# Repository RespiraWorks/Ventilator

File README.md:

# RespiraWorks Open Source Ventilator

</br>

This is a common repository for all hardware and software components of the RespiraWorks open source ventilator.

**If you intend to contribute, please read our [wiki](https://github.com/RespiraWorks/Ventilator/wiki) and [agreement](https://respiraworks.github.io/Ventilator/contributing/contributing.html).**

[RespiraWorks](https://respira.works/) is a 501(c)(3) non-profit organization with over 200 contributors worldwide working to design a low-cost and [open-source](open_source.md) ventilator for communities underserved by the global supply chain. Our objective is to provide the know-how and technology to enable local enterprises to manufacture and service these systems.

|           Most recent v0.4 rendering            |            Assembled v0.3 prototype             |
|:-----------------------------------------------:|:-----------------------------------------------:|
|  |  |

## Design Goals

We are dedicated to making this ventilator:
* [fully open source (software and hardware)](open_source.md)
* affordable (materials cost under US$2000)
* fully featured for extended clinical use through weaning and recovery
* vetted and filing-ready for regulatory review around the world
* optimized bill of materials to account for constrained supply chains
* designed for long-term clinical use beyond the pandemic

Most low-cost ventilator designs that have emerged in light of the COVID-19 crisis tackle the 'bridge' problem — keeping a patient alive for 6-8 hours of closely monitored care until they can be transitioned to a fully featured ventilator. We are designing that full ventilator, a highly valued medical device critical to care beyond the current crisis.

Our design shall provide essential features such as an intuitive, localized user interface, adaptive pressure- and volume-based operating modes, fine control of oxygen concentration, High Flow Nasal Cannula and other advanced features. What sets us apart from other similarly ambitious projects is our dedication to being fully open source. This repository embodies that promise.

We are targeting middle- and low-income parts of the world that will deal with COVID-19 for longer, with less access to healthcare, and a larger deficit of medical devices. We aim to deliver a design which meets the same operational rigors of current commercial ventilators, while addressing the high barrier to entry for such devices.

If you can lend your skills towards achieving this goal, please contact us at [join-us@respira.works](mailto:join-us@respira.works?subject=[GitHub]%20Join%20request). A list of roles we are looking to fill is also on our [website](https://respira.works/join-us).

## Project Status / Disclaimers

**This is an incomplete, as yet untested design that is not intended to be used on patients.**

**The repository contains live documents. There may be incomplete or contradictory information about various aspects of the design. Components may or may not connect and integrate as intended. Contents may also be out of date. If you decide to buy or build anything, do so at your own risk.**

We are currently in the process of designing our v0.4 prototype, plans whereof are captured in some of our outstanding [Milestones](https://github.com/RespiraWorks/Ventilator/milestones). The `master` branch of this repository includes bleeding edge changes in electrical, mechanical and software aspects of the project. Browse at your own peril.

For the latest stable and tested (but also obsolete) version of the design see the [Releases](https://github.com/RespiraWorks/Ventilator/releases) page.

## Repository Structure

* [**Documentation pages (outside of repository)**](https://respiraworks.github.io/Ventilator/index.html) - auto-generated pages (should eventually) include:
  * Requirements documentation
  * Regulatory documentation
  * Software documentation
  * Bill of materials for manufacturing
* [**Documentation source**](docs) - source files for the above pages
* [**System Design**](design) - describes the functional implementation and design theory of the system
* [**Manufacturing Design**](manufacturing) - describes the physical design of the ventilator and its components. Includes CAD models and notes on the manufacturing process
* [**Main Circuit Board**](pcb) - design, materials, assembly instructions for the ventilator main circuit board
* [**Software**](software) - source code for cycle controller and user interface, debug tools, and test scripts. Software architecture documentation is also here.
* [**Quality Assurance**](quality-assurance) - quality assurance strategy, testing plans, data

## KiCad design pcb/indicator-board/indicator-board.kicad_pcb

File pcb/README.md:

# Ventilator Mainboard 

This directory contains files for the Ventilator mainboard design.

The RespiraWorks Ventilator Mainboard PCB is a custom component that integrates the Cycle Controller, UI Computer,
sensors, actuator drives, power supplies, filtering, and protection components.

Due to the coupled nature of the controls, electrical, and mechanical components and their design the RespiraWorks
ventilator contains a custom fabricated printed circuit board (PCB) to connect the microcontroller, interface processor,
and sensor interfaces. The use of a custom PCB greatly reduces the chance for electrical assembly and fabrication errors
and is far more amenable to a quality fabrication process than hand-soldered components. We do not intend for this
component to be hand-assembled, and engineering turnkey fabrication instructions have been generated as part of the
submission; no assembly instructions are provided here.

The original Rev 1 PCB was done in Altium.  As of Rev A, this project has moved to KiCad for better accessibility.

## Rev A

The latest revision of the PCB is Rev A, designed to be used in the top-level design revision Ventilator v0.4.

The main design is in this folder and the project file is here: [Ventilator Mainboard Rev A](Ventilator.pro)

Recently exported files for PCB manufacture can be found on our Google Drive at
[Manufacturing/Output files v0.4/PCB](https://tinyurl.com/2p8af3fm).

This revision integrates many of the modules and daughter-cards in PCB Rev 1.0 into a single PCB, while breaking out the sensors to daughter-cards to make it better adaptable to sensors available in other markets.  It adds some important new features:
 - Moved CycleController from STM32L452 to STM32L496 microcontroller for more I/O pins, memory, and storage.
 - Added an independent FPGA-based supervisor.
 - Higher power capability now up to 120W.
 - Self-powered power loss alarm.
 - Integrated stepper drivers.
 - Ambient pressure sensing for altitude compensation.
 - Real time clock capability.
 - EEPROM for storing calibration data.
 - Additional pressure sensor channels to enable nested flow control.
 - Temperature sensors to monitor component health.
 - Integrated Li-Ion battery backup, charging, and monitoring.
 - Additional power connections for display, fans, and indicator lights.

## Sensor daughter-boards

> TODO: add documentation about these

## Rev 1.0

An archive of the previous version of the PCB, including the Altium-based design project and a snapshot of the old
readme is available on our Google Drive at
[Manufacturing/Output files v0.2-0.3/PCB](https://drive.google.com/drive/folders/1xHPLvo59tGI5uU38FrWMkVGmK_UR2sjQ?usp=sharing)

## Current issues

Issues for PCB work are tracked by tickets with the [PCB label](https://github.com/RespiraWorks/Ventilator/labels/pcb).

Somewhat related are the [Electrical design](https://github.com/RespiraWorks/Ventilator/labels/Electrical) issues.

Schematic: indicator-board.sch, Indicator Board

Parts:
D1, D2, D5: Green; LED_0805_2012Metric; Manufacturer PN LTST-C171KGKT
D3, D6: Yellow; LED_0805_2012Metric; Manufacturer PN LTST-C170KSKT
D4, D7: Red; LED_0805_2012Metric; Manufacturer PN LTST-C170KRKT
H1, H2, H3, H4: M2.5; MountingHole_2.7mm
J1: Cable to from main board; Molex_Micro-Fit_3.0_43650-0815_1x08_P3.00mm_Vertical; Manufacturer PN 43650-0815
R1, R2, R3, R4, R5, R6, R7: 1k; R_0603_1608Metric; Manufacturer PN RC0603FR-071KL

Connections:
+5V: J1.2, R1.1
/CC-LED-G: J1.3, R2.1
/CC-LED-R: J1.4, R4.1
/CC-LED-Y: J1.5, R3.1
/UI-LED-G: J1.6, R5.1
/UI-LED-R: J1.7, R7.1
/UI-LED-Y: J1.8, R6.1
GND: D1.1 (K), D2.1 (K), D3.1 (K), D4.1 (K), D5.1 (K), D6.1 (K), D7.1 (K), J1.1
unnamed: D1.2 (A), R1.2
unnamed: D2.2 (A), R2.2
unnamed: D3.2 (A), R3.2
unnamed: D4.2 (A), R4.2
unnamed: D5.2 (A), R5.2
unnamed: D6.2 (A), R6.2
unnamed: D7.2 (A), R7.2

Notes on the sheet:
Cycle Controller LEDs
UI Computer LEDs
Power LED

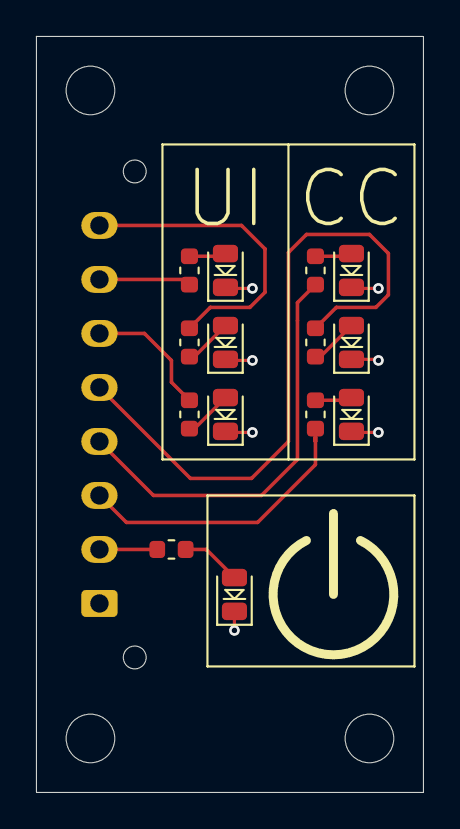
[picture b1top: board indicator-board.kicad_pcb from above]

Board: 4 copper layers, 21.5 x 42.0 mm, 19 parts (1 on the bottom side), 15 nets.

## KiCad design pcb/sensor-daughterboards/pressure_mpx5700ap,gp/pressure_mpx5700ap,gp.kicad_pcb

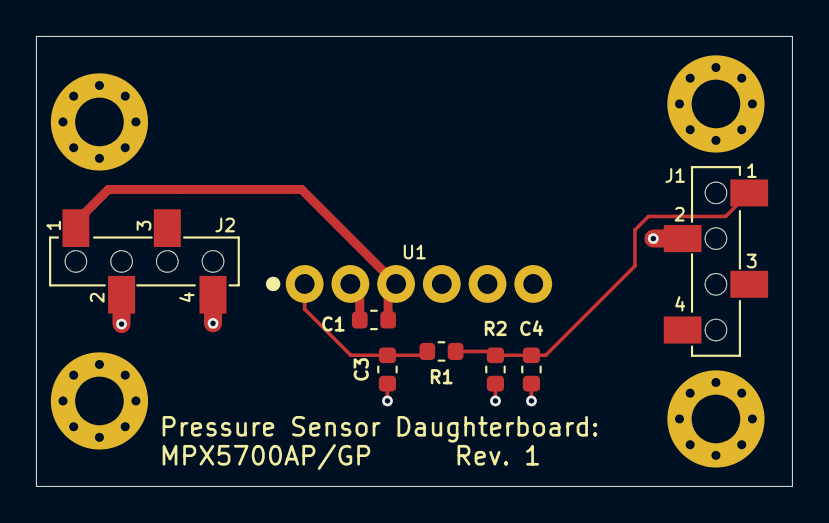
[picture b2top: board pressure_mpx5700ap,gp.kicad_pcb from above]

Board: 2 copper layers, 42.0 x 25.0 mm, 12 parts (0 on the bottom side), 4 nets.

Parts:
C1, C4: 1uF; C_0603_1608Metric
C3: 470pF; C_0603_1608Metric
H1, H2, H3, H4: M2.5; MountingHole_2.7mm_M2.5_Pad_Via
J1, J2: Main board connections (bottom entry); PinSocket_1x04_P2.54mm_Vertical_SMD_TE_1241152-4
R1: 2.4K; R_0603_1608Metric
R2: 4.7K; R_0603_1608Metric
U1: MPX5700AP/GP; NXP_MPX5700AP,GP_Vertical

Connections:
+5V_Sns: C1.2, J2.1, U1.3
GND: C1.1, C3.1, C4.1, J1.2, J2.2, J2.4, R2.1, U1.2
unnamed: C3.2, R1.2, U1.1
unnamed: C4.2, J1.1, R1.1, R2.2

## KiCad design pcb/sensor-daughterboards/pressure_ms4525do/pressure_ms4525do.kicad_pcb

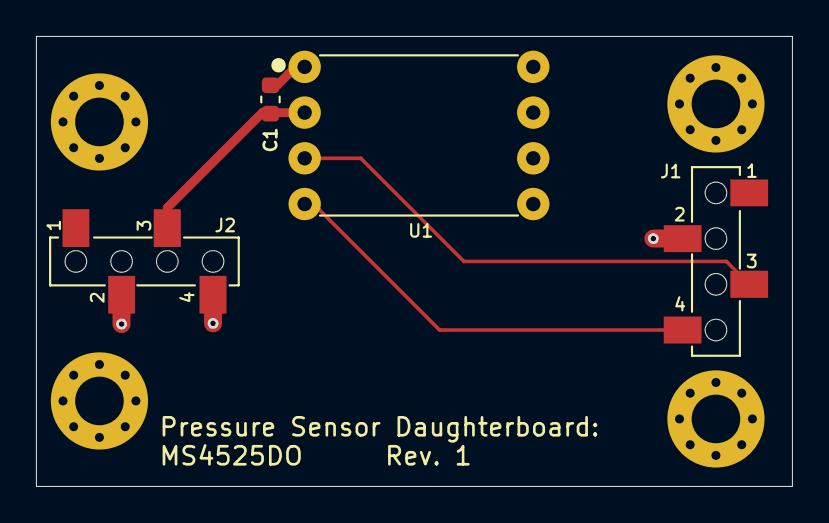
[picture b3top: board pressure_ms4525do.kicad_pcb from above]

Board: 2 copper layers, 42.0 x 25.0 mm, 8 parts (0 on the bottom side), 4 nets.

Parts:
C1: 1uF; C_0603_1608Metric
H1, H2, H3, H4: M2.5; MountingHole_2.7mm_M2.5_Pad_Via
J1, J2: Main board connections (bottom entry); PinSocket_1x04_P2.54mm_Vertical_SMD_TE_1241152-4
U1: MS4525DO-DS5AI001DP; TE_MS4525DO-DSxxxxxxDP

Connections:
+3.3V_Sns: C1.2, J2.3, U1.2
/SCL: J1.4, U1.4
/SDA: J1.3, U1.3
GND: C1.1, J1.2, J2.2, J2.4, U1.1

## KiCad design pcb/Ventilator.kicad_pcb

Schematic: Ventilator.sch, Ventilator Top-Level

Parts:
C186: 1uF; C_0603_1608Metric; Voltage 50V; Manufacturer PN C0805C105K5RACTU
D1: BAT54J; D_SOD-323F; Manufacturer PN BAT54J,115
F5: 1.1A 16V; Fuse_1812_4532Metric_Castellated; Manufacturer PN 0ZCG0110AF2C
H10, H11, H12, H13, H14: MountingHole_Pad; MountingHole_4.5mm_Pad
J53: Fan; Molex_Micro-Fit_3.0_43650-0215_1x02_P3.00mm_Vertical; Manufacturer PN 43650-0215
JP1, JP2, JP3: Jumper_NC_Small; SolderJumper-2_P1.3mm_Bridged_RoundedPad1.0x1.5mm
Q1, Q2: MMBT3904; SOT-23; Manufacturer PN MMBT3904-7-F
R1, R2, R3, R4, R5, R6, R7, R8: 1k; R_0603_1608Metric
R9, R18, R19: 4.7k; R_0603_1608Metric
R10, R11, R12, R13, R14, R15, R16, R17: 100k; R_0603_1608Metric
TP1, TP2, TP3, TP4, TP5, TP6, TP10, TP11, TP12, TP13, TP14, TP15, TP16, TP17, TP23, TP24, TP25, TP26, TP27, TP28, TP29, TP30, TP31, TP32, TP33, TP34: TP; TestPoint_Pad_2.0x2.0mm
TP7: PG-12V; TestPoint_Pad_2.0x2.0mm
TP8: PMon-IBat; TestPoint_Pad_2.0x2.0mm
TP9: PMon-IAdp; TestPoint_Pad_2.0x2.0mm
TP20: UART-Rx-STM-Tx-STLink; TestPoint_Pad_2.0x2.0mm
TP21: UART-Tx-STM-Rx-STLink; TestPoint_Pad_2.0x2.0mm
TP22: FPGA-ADC-nInt; TestPoint_Pad_2.0x2.0mm
TP35: PSol-CS1; TestPoint_Pad_2.0x2.0mm
TP36: CC-SDA; TestPoint_Pad_2.0x2.0mm
TP38: CC-SCL; TestPoint_Pad_2.0x2.0mm
TP39, TP40, TP41, TP42, TP44, TP45, TP46, TP47, TP50, TP51, TP52, TP53: TestPoint_Flag; TestPoint_Keystone_5019_Minature; Manufacturer PN 5019
TP43: PSol-CS2; TestPoint_Pad_2.0x2.0mm
TP48: UART-RTS-STM-CTS-RPi; TestPoint_Pad_2.0x2.0mm
TP49: UART-CTS-STM-RTS-RPi; TestPoint_Pad_2.0x2.0mm
TP54: UART-Tx-RPi-Rx-STM; TestPoint_Pad_2.0x2.0mm
TP55: UART-Rx-RPi-Tx-STM; TestPoint_Pad_2.0x2.0mm

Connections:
+3.3V_Ctrl: D1.1 (K), JP3.1, R5.2, R9.1, R18.1, R19.1; also elsewhere on the board
+12V: C186.1, F5.2; also elsewhere on the board
/Add'l aux functions/Blower-Enable: JP3.2; also elsewhere on the board
/Aux-I2C-Switch-nINT: JP2.2; also elsewhere on the board
/Bat-Alert: R3.1; also elsewhere on the board
/CC-SCL: R19.2, TP38.1; also elsewhere on the board
/CC-SDA: R18.2, TP36.1; also elsewhere on the board
/CC-Stepper-Reset: R4.1; also elsewhere on the board
/Cycle Controller/PH0: JP1.1, JP2.1, R9.2; also elsewhere on the board
/Exh-Flow: R11.2; also elsewhere on the board
/FPGA's ADC/ADC0: R10.1; also elsewhere on the board
/FPGA's ADC/ADC1: R11.1; also elsewhere on the board
/FPGA's ADC/ADC2: R12.1; also elsewhere on the board
/FPGA's ADC/ADC3: R13.1; also elsewhere on the board
/FPGA's ADC/ADC4: R14.1; also elsewhere on the board
/FPGA's ADC/ADC5: R15.1; also elsewhere on the board
/FPGA's ADC/ADC6: R16.1; also elsewhere on the board
/FPGA's ADC/ADC7: R17.1; also elsewhere on the board
/FPGA's ADC/nINT: TP22.1; also elsewhere on the board
/FPGA-Stepper-Reset: R6.2; also elsewhere on the board
/Inh-Flow: R10.2; also elsewhere on the board
/Low-Alarm-Bat: D1.2 (A), R2.1; also elsewhere on the board
/Mixing-Tank-Pressure: R15.2
/Oxygen-FiO2: R16.2; also elsewhere on the board
/Oxygen-Flow: R12.2; also elsewhere on the board
/Oxygen-Pressure: R14.2; also elsewhere on the board
/PSol Driver, Spare/CS: TP43.1; also elsewhere on the board
/PSol Driver/CS: TP35.1; also elsewhere on the board
/Patient-Pressure: R13.2; also elsewhere on the board
/Power Entry / Battery Handling/PG-12V: TP7.1; also elsewhere on the board
/Power Entry / Battery Handling/PMon-IAdp: TP9.1; also elsewhere on the board
/Power Entry / Battery Handling/PMon-IBat: TP8.1; also elsewhere on the board
/Safety FPGA/DIFF-RX-7+: TP31.1; also elsewhere on the board
/Safety FPGA/DIFF-RX-7-: TP32.1; also elsewhere on the board
/Safety FPGA/DIFF-RX-8+: TP29.1; also elsewhere on the board
/Safety FPGA/DIFF-RX-8-: TP30.1; also elsewhere on the board
/Safety FPGA/DIFF-RX-9+: TP27.1; also elsewhere on the board
/Safety FPGA/DIFF-RX-9-: TP28.1; also elsewhere on the board
/Safety FPGA/DIFF-RX-A+: TP25.1; also elsewhere on the board
/Safety FPGA/DIFF-RX-A-: TP26.1; also elsewhere on the board
/Safety FPGA/DIFF-RX-B+: TP23.1; also elsewhere on the board
/Safety FPGA/DIFF-RX-B-: TP24.1; also elsewhere on the board
/Safety FPGA/GPIO-11: TP33.1; also elsewhere on the board
/Safety FPGA/GPIO-12: TP34.1; also elsewhere on the board
/Stepper-nReset: Q1.3, Q2.3, R5.1; also elsewhere on the board
/SysMonADC-nINT: JP1.2; also elsewhere on the board
/UART-CTS-STM-RTS-RPi: TP49.1
/UART-RTS-RPi-CTS-STM: R1.1; also elsewhere on the board
/UART-RTS-STM-CTS-RPi: TP48.1
/UART-Rx-RPi-Tx-STM: TP55.1; also elsewhere on the board
/UART-Rx-STM-Tx-STLink: TP20.1; also elsewhere on the board
/UART-Tx-FPGA-Rx-RPi: R7.2; also elsewhere on the board
/UART-Tx-RPi-Rx-STM: R8.2, TP54.1; also elsewhere on the board
/UART-Tx-STM-Rx-STLink: TP21.1; also elsewhere on the board
/UI Computer/GPIO0(ID_SD): TP10.1; also elsewhere on the board
/UI Computer/GPIO1(ID_SC): TP11.1; also elsewhere on the board
/UI Computer/GPIO2(SDA): TP12.1; also elsewhere on the board
/UI Computer/GPIO3(SCL): TP13.1; also elsewhere on the board
/UI Computer/GPIO7(CE1): TP14.1; also elsewhere on the board
/UI Computer/GPIO9(MISO): R7.1; also elsewhere on the board
/UI Computer/GPIO10(MOSI): TP15.1; also elsewhere on the board
/UI Computer/GPIO11(SCLK): TP16.1; also elsewhere on the board
/UI Computer/GPIO13(PWM1): TP17.1; also elsewhere on the board
/UI Computer/GPIO14(TXD): R8.1; also elsewhere on the board
/UI Computer/GPIO17: R1.2; also elsewhere on the board
/UI Computer/GPIO18(PCM_CLK): R2.2; also elsewhere on the board
/UI Computer/GPIO19(PCM_FS): R3.2; also elsewhere on the board
/UI Computer/GPIO20(PCM_DIN): TP1.1; also elsewhere on the board
/UI Computer/GPIO21(PCM_DOUT): TP2.1; also elsewhere on the board
/UI Computer/GPIO22: TP3.1; also elsewhere on the board
/UI Computer/GPIO23: TP4.1; also elsewhere on the board
/UI Computer/GPIO24: TP5.1; also elsewhere on the board
/UI Computer/GPIO27: TP6.1; also elsewhere on the board
/Vin-Sense: R17.2; also elsewhere on the board
GND: C186.2, J53.1, Q1.2, Q2.2, TP39.1, TP40.1, TP41.1, TP42.1, TP44.1, TP45.1, TP46.1, TP47.1, TP50.1, TP51.1, TP52.1, TP53.1; also elsewhere on the board
unnamed: F5.1, J53.2
unnamed: Q1.1, R4.2
unnamed: Q2.1, R6.1

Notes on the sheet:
Series resistors prevent FPGA ADC faults from disrupting critical analog signals
Either cycle controller or FPGA can shut down stepper drivers
Series resistors on signals received by UI computer prevents problems driving these signals if UI computer loses power
Unless noted otherwise: - Resistors are 1% tolerance - Capacitors < 47 nF are 5% tolerance - Capacitors ≥ 47 nF are 10% tolerance
Global I2C pull-ups

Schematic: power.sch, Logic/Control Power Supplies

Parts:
C1: 33uF; CP_Elec_6.3x7.7; Voltage 50V; Manufacturer PN EEE-FK1H330XP
D2, D3: BAT54J; D_SOD-323F; Manufacturer PN BAT54J,115
Q3: MMBT3904; SOT-23; Manufacturer PN MMBT3904-7-F
R20, R21: 1k; R_0603_1608Metric
R22: 0; R_0603_1608Metric
TP56: TP; TestPoint_Pad_2.0x2.0mm
TP57, TP58: TestPoint_Flag; TestPoint_Keystone_5019_Minature; Manufacturer PN 5019

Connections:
+5V: D2.2 (A), R22.1; also elsewhere on the board
+5V_Sns: C1.1, R22.2, TP58.1; also elsewhere on the board
+5V_USB: D3.2 (A); also elsewhere on the board
/Logic/Control Power Supplies/3.3V Logic Supply/In: D2.1 (K), D3.1 (K), TP57.1; also elsewhere on the board
/Logic/Control Power Supplies/5V UI Supply/nEnable: Q3.3; also elsewhere on the board
/UI-Power-Off: R20.1, R21.1, TP56.1; also elsewhere on the board
GND: C1.2, Q3.2, R20.2; also elsewhere on the board
unnamed: Q3.1, R21.2

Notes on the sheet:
Optional filter
5V Power Supplies
Diode-ORing for +3.3V Ctrl, so that the CC can be powered from the STM programmer's USB connection alone, for programming and firmware debug
3.3V Power Supplies

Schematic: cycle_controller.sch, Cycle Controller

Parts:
BT1: CR2016; BatteryHolder_CR2016_MPD_BLP2016SM-G; Manufacturer PN BLP2016SM-GTR
C26, C32, C36, C37, C38, C39, C40, C41, C43: 100nF; C_0603_1608Metric; Voltage 50V; Manufacturer PN C0603C104K5RACTU
C27, C28: TBD; C_0603_1608Metric
C29, C30: 18pF; C_0603_1608Metric; Voltage 50V; Manufacturer PN C0603C180J5GACTU
C31, C35, C44: 1uF; C_0603_1608Metric; Voltage 50V; Manufacturer PN C0805C105K5RACTU
C33, C34: 6.8pF; C_0603_1608Metric; Voltage 50V; Manufacturer PN C0603C689J5GACTU
C42: 10uF; C_1210_3225Metric; Voltage 100V; Manufacturer PN GRM32EC72A106KE05L
J1: Optical end stop 1; Molex_Micro-Fit_3.0_43650-0315_1x03_P3.00mm_Vertical; Manufacturer PN 43650-0315
J2: Optical end stop 2; Molex_Micro-Fit_3.0_43650-0315_1x03_P3.00mm_Vertical; Manufacturer PN 43650-0315
J3: 503182-1852; SD_Molex_5031821852; Manufacturer PN 503182-1852
J4, J7: Arduino Connector; PinSocket_1x08_P2.54mm_Vertical; Manufacturer PN PPPC081LFBN-RC
J5: Arduino Connector; PinSocket_1x06_P2.54mm_Vertical; Manufacturer PN PPPC061LFBN-RC
J6: Arduino Connector; PinSocket_1x10_P2.54mm_Vertical; Manufacturer PN PPPC101LFBN-RC
JP6: Jumper; SolderJumper-2_P1.3mm_Open_RoundedPad1.0x1.5mm
JP7: Jumper; SolderJumper-2_P1.3mm_Bridged_RoundedPad1.0x1.5mm
R37, R44: 10k; R_0603_1608Metric
R38: 100; R_0603_1608Metric
R39, R40, R42, R43, R45, R46, R47, R48, R49: 0; R_0603_1608Metric
R41: 4.7k; R_0603_1608Metric
SW1: User TBD; SW_Push_6x6; Manufacturer PN PTS645SK50SMTR92 LFS
SW2: Reset CC; SW_Push_6x6; Manufacturer PN PTS645SK50SMTR92 LFS
TP67: SPI-MISO; TestPoint_Pad_2.0x2.0mm
TP68: SPI-MOSI; TestPoint_Pad_2.0x2.0mm
TP69: SPI-SCLK; TestPoint_Pad_2.0x2.0mm
TP70: uSD-nCS; TestPoint_Pad_2.0x2.0mm
TP71: PD3; TestPoint_Pad_2.0x2.0mm
TP72: PD4; TestPoint_Pad_2.0x2.0mm
TP73: PD5; TestPoint_Pad_2.0x2.0mm
TP74: PD6; TestPoint_Pad_2.0x2.0mm
TP75: PE0; TestPoint_Pad_2.0x2.0mm
TP76: PE1; TestPoint_Pad_2.0x2.0mm
TP77: PE2; TestPoint_Pad_2.0x2.0mm
TP78: PE3; TestPoint_Pad_2.0x2.0mm
U5: STM32L496VGT; LQFP-100_14x14mm_P0.5mm; Manufacturer PN STM32L496VGT6
U31: ShieldConnectors; stm32shield
Y1: 8 Mhz; Crystal_SMD_HC49-SD; Manufacturer PN ABLS-8.000MHZ-B4-T
Y2: 32.768 kHz; Crystal_SMD_Abracon_ABS25; Manufacturer PN ABS25-32.768KHZ-6-T

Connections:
+3.3V_Ctrl: C31.1, C32.1, C38.1, C39.1, C40.1, C41.1, C42.1, J3.4 (VDD), J4.2, J4.4, JP6.2, R37.1, R41.2, U5.11, U5.28, U5.50, U5.73, U5.75, U5.100; also elsewhere on the board
+3.3V_Ctrl_A: J6.8
+3.3V_Sns: C43.1, C44.1, R45.2, U5.22; also elsewhere on the board
+5V: J1.1, J4.5, J4.8; also elsewhere on the board
/Bat-Alert: U5.77; also elsewhere on the board
/Blower-Ctrl: U5.63; also elsewhere on the board
/CC-Buzzer: J7.6, U5.53; also elsewhere on the board
/CC-LED-G: J5.3, U5.67; also elsewhere on the board
/CC-LED-R: U5.65; also elsewhere on the board
/CC-LED-Y: U5.66; also elsewhere on the board
/CC-SCL: J6.10, U5.95; also elsewhere on the board
/CC-SDA: J6.9, U5.96; also elsewhere on the board
/CC-Stepper-Reset: J7.3, U5.48; also elsewhere on the board
/Cycle Controller/BOOT0: R44.2, U5.94
/Cycle Controller/PH0: R42.1, U5.12; also elsewhere on the board
/Cycle Controller/RTC-Batt: BT1.1 (+), C35.1, JP6.1, U5.6
/Cycle Controller/Stepper-Lim-Sw1: C27.2, R39.1, U5.78
/Cycle Controller/Stepper-Lim-Sw2: C28.2, R40.1, U5.79
/Cycle Controller/USD-MISO: J6.5
/Cycle Controller/USD-MOSI: J6.4
/Cycle Controller/USD-SCLK: J6.6
/Cycle Controller/uSD-Detect: J3.Detect (DT), R37.2, U5.64
/Cycle Controller/uSD-nCS: J3.2 (CD/DAT3), TP70.1, U5.29
/Exh-Flow: U5.33; also elsewhere on the board
/Inh-Flow: J5.2, U5.24; also elsewhere on the board
/Mix-Tank-Pressure: U5.17; also elsewhere on the board
/Oxygen-FiO2: J5.6, U5.15; also elsewhere on the board
/Oxygen-Flow: U5.34; also elsewhere on the board
/Oxygen-Pressure: U5.18; also elsewhere on the board
/PMon-ACOK: J5.4, U5.92; also elsewhere on the board
/PSol1-Ctrl: J6.1, U5.47; also elsewhere on the board
/PSol1-nFault: U5.93; also elsewhere on the board
/PSol2-Ctrl: U5.23; also elsewhere on the board
/PSol2-nFault: R43.1, U5.13; also elsewhere on the board
/Patient-Pressure: J5.5, U5.16; also elsewhere on the board
/STM Programmer for cycle controller/CC-SWCLK: U5.76; also elsewhere on the board
/STM Programmer for cycle controller/CC-SWDIO: U5.72; also elsewhere on the board
/STM Programmer for cycle controller/CC-SWO: U5.89; also elsewhere on the board
/STM Programmer for cycle controller/CC-nRST: C37.1, J4.3, SW2.1, U5.14; also elsewhere on the board
/Stepper1-StCk: U5.35; also elsewhere on the board
/Stepper1-nBusy: J6.3, U5.51; also elsewhere on the board
/Stepper2-StCk: J7.8, U5.36; also elsewhere on the board
/Stepper2-nBusy: J6.2, U5.52; also elsewhere on the board
/Stepper-MISO: J3.7 (DAT0), TP67.1, U5.31; also elsewhere on the board
/Stepper-MOSI: J3.3 (CMD), TP68.1, U5.32; also elsewhere on the board
/Stepper-SCK: J3.5 (CLK), TP69.1, U5.30; also elsewhere on the board
/Stepper-nCS: J7.5, U5.54; also elsewhere on the board
/Stepper-nFlag: J7.4, U5.37; also elsewhere on the board
/UART-CTS-RPi-RTS-STM: U5.71; also elsewhere on the board
/UART-CTS-STM-RTS-FPGA: U5.91; also elsewhere on the board
/UART-RTS-RPi-CTS-STM: U5.70; also elsewhere on the board
/UART-RTS-STM-CTS-FPGA: U5.90; also elsewhere on the board
/UART-Rx-RPi-Tx-STM: J7.2, U5.68; also elsewhere on the board
/UART-Rx-STM-Tx-FPGA: U5.83; also elsewhere on the board
/UART-Rx-STM-Tx-STLink: U5.26; also elsewhere on the board
/UART-Tx-RPi-Rx-STM: J7.1, U5.69; also elsewhere on the board
/UART-Tx-STM-Rx-FPGA: U5.80; also elsewhere on the board
/UART-Tx-STM-Rx-STLink: J7.7, U5.25; also elsewhere on the board
GND: BT1.2 (-), C27.1, C28.1, C29.1, C30.1, C31.2, C32.2, C33.2, C34.2, C35.2, C36.2, C37.2, C38.2, C39.2, C40.2, C41.2, C42.2, J1.3, J2.3, J3.6 (VSS), J3.9 (Shield), J4.6, J4.7, J6.7, JP7.1, R38.2, R44.1, R46.1, R47.1, SW1.2, SW2.2, U5.10, U5.27, U5.49, U5.74, U5.99; also elsewhere on the board
GNDA: C43.2, C44.2, JP7.2, U5.19, U5.20
unnamed: C26.1, R41.1, SW1.1, U5.7
unnamed: C26.2, R38.1
unnamed: C29.2, R42.2, Y1.1
unnamed: C30.2, R43.2, Y1.2
unnamed: C33.1, R47.2, R48.2, Y2.1
unnamed: C34.1, R46.2, R49.2, Y2.4
unnamed: C36.1, R45.1, U5.21
unnamed: J1.2, J2.1, R39.2
unnamed: J2.2, R40.2
unnamed: R48.1, U5.8
unnamed: R49.1, U5.9
unnamed: TP71.1, U5.84
unnamed: TP72.1, U5.85
unnamed: TP73.1, U5.86
unnamed: TP74.1, U5.87
unnamed: TP75.1, U5.97
unnamed: TP76.1, U5.98
unnamed: TP77.1, U5.1
unnamed: TP78.1, U5.2

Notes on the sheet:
VDD pins
VDDA pin
Boots from main Flash memory by default
MicroSD Card Connector
Arduino headers for expansion
D10
D11
D12
D13
D18/SDA
D19/SCL
AREF
VIN
IOREF
RESET
Uses MSI internal 4 Mhz clock by default

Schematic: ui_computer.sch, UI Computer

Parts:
C45: 100nF; C_0603_1608Metric; Voltage 50V; Manufacturer PN C0603C104K5RACTU
C46: 1uF; C_0603_1608Metric; Voltage 50V; Manufacturer PN C0805C105K5RACTU
H1: RaspberryPi
J8: Raspberry Pi; PinSocket_2x20_P2.54mm_Vertical; Manufacturer PN ESQ-120-44-L-D
J9: Touchscreen power; Molex_Micro-Fit_3.0_43045-0212_2x01_P3.00mm_Vertical; Manufacturer PN 43045-0212
R50, R51, R52, R53: 0; R_0603_1608Metric

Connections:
+3V3_Rpi: J8.1, J8.17, R50.1, R52.1
+5V_GUI: C45.1, C46.1, J8.2, J8.4, J9.2; also elsewhere on the board
/GUI-Buzzer: J8.32; also elsewhere on the board
/UART-CTS-RPi-RTS-STM: J8.36; also elsewhere on the board
/UART-Rx-FPGA-Tx-RPi: J8.24; also elsewhere on the board
/UART-Rx-RPi-Tx-STM: J8.10; also elsewhere on the board
/UI Computer/GPIO0(ID_SD): J8.27; also elsewhere on the board
/UI Computer/GPIO1(ID_SC): J8.28; also elsewhere on the board
/UI Computer/GPIO2(SDA): J8.3; also elsewhere on the board
/UI Computer/GPIO3(SCL): J8.5; also elsewhere on the board
/UI Computer/GPIO7(CE1): J8.26; also elsewhere on the board
/UI Computer/GPIO9(MISO): J8.21; also elsewhere on the board
/UI Computer/GPIO10(MOSI): J8.19; also elsewhere on the board
/UI Computer/GPIO11(SCLK): J8.23; also elsewhere on the board
/UI Computer/GPIO13(PWM1): J8.33; also elsewhere on the board
/UI Computer/GPIO14(TXD): J8.8; also elsewhere on the board
/UI Computer/GPIO17: J8.11; also elsewhere on the board
/UI Computer/GPIO18(PCM_CLK): J8.12; also elsewhere on the board
/UI Computer/GPIO19(PCM_FS): J8.35; also elsewhere on the board
/UI Computer/GPIO20(PCM_DIN): J8.38; also elsewhere on the board
/UI Computer/GPIO21(PCM_DOUT): J8.40; also elsewhere on the board
/UI Computer/GPIO22: J8.15; also elsewhere on the board
/UI Computer/GPIO23: J8.16; also elsewhere on the board
/UI Computer/GPIO24: J8.18; also elsewhere on the board
/UI Computer/GPIO27: J8.13; also elsewhere on the board
/UI Computer/UI_ID0: J8.22, R52.2, R53.1
/UI Computer/UI_ID1: J8.37, R50.2, R51.1
/UI-LED-G: J8.7; also elsewhere on the board
/UI-LED-R: J8.29; also elsewhere on the board
/UI-LED-Y: J8.31; also elsewhere on the board
GND: C45.2, C46.2, H1.1, J8.6, J8.9, J8.14, J8.20, J8.25, J8.30, J8.34, J8.39, J9.1, R51.2, R53.2; also elsewhere on the board

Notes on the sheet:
RPI powered by 5V
USB TO UART adapter: https://www.ftdichip.com/Support/Documents/DataSheets/Modules/DS_DB9-USB-RS232.pdf

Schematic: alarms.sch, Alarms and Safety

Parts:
C47, C50, C53: 100nF; C_0603_1608Metric; Voltage 50V; Manufacturer PN C0603C104K5RACTU
C48: 33uF; CP_Elec_6.3x7.7; Voltage 50V; Manufacturer PN EEE-FK1H330XP
C49: 1uF; C_0603_1608Metric; Voltage 50V; Manufacturer PN C0805C105K5RACTU
C51, C52, C54, C55: 10nF; C_0603_1608Metric; Voltage 50V; Manufacturer PN GRM1885C1H103JA01D
D8: 2.0V; D_SOD-123; Manufacturer PN MMSZ4679T1G
D9, D10: 3.3V; D_SOD-123; Manufacturer PN MMSZ4684T1G
D11, D12, D13, D14: 1N4448W; D_SOD-123; Manufacturer PN 1N4448W-7-F
J10: Alarm Battery (4x AA); Molex_Micro-Fit_3.0_43650-0415_1x04_P3.00mm_Vertical; Manufacturer PN 43650-0415
Q4, Q5, Q6, Q8, Q9, Q11, Q12, Q13: MMBT3904; SOT-23; Manufacturer PN MMBT3904-7-F
Q7, Q10: MMBT2907A; SOT-23; Manufacturer PN MMBT2907A-7-F
R54, R55, R56, R57, R58, R59, R60, R61, R65, R68, R76, R81, R84: 10k; R_0603_1608Metric
R62, R77, R78: 1M; R_0603_1608Metric
R63, R66, R71, R72: 100k; R_0603_1608Metric
R64: 2k; R_0603_1608Metric
R67: 442k; R_0603_1608Metric
R69: 52.3k; R_0603_1608Metric
R70: 249k; R_0603_1608Metric
R73, R74, R79, R80, R82, R83, R85, R86: 1k; R_0603_1608Metric
R75: 680; R_0603_1608Metric
S1, S2, S3, S4: CT-1205H-SMT; CT-1205H-SMT-TR; Manufacturer PN CT-1205H-SMT-TR
TP79: PD-Alarm; TestPoint_Pad_2.0x2.0mm
TP80, TP81, TP82, TP83, TP84, TP85: TP; TestPoint_Pad_2.0x2.0mm
U6, U7: TLC555; SOIC-8_3.9x4.9mm_P1.27mm; Manufacturer PN TLC555QDR
U8: TL431LI; SOT-23; Manufacturer PN TL431LIAIDBZR

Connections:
+3.3V_Ctrl: D8.1 (K); also elsewhere on the board
+5V: D9.1 (K), D10.1 (K), D11.2 (A), S2.1, S3.1; also elsewhere on the board
+5V_GUI: S4.1; also elsewhere on the board
+BATT: C48.1, C50.2, C53.2, D11.1 (K), Q7.3, Q10.2, R56.2, R61.2, R66.2, R69.2, R75.2, S1.1, U6.8 (VCC), U7.8 (VCC)
/Alarms and Power Monitoring/Alarm-Bat: D14.2 (A), J10.1, R71.1
/Alarms and Power Monitoring/Low-Alarm-Bat: Q10.3, R78.1, R81.1, R84.1, TP84.1
/Alarms and Power Monitoring/PD-Alarm: C47.2, D12.1 (K), D13.1 (K), R63.2, TP79.1, U6.4 (Reset)
/CC-Buzzer: R79.1, TP82.1; also elsewhere on the board
/FPGA-Buzzer: R82.1, TP83.1; also elsewhere on the board
/GUI-Buzzer: R85.1, TP85.1; also elsewhere on the board
/Low-Alarm-Bat: R84.2; also elsewhere on the board
GND: C47.1, C48.2, C49.1, C50.1, C51.1, C52.1, C53.1, C54.1, C55.1, J10.3, Q4.2, Q5.2, Q6.2, Q8.2, Q9.2, Q11.2, Q12.2, Q13.2, R54.1, R57.1, R58.1, R63.1, R72.2, R74.2, R80.2, R81.2, R83.2, R86.2, U6.1 (GND), U7.1 (GND), U8.3 (A); also elsewhere on the board
unnamed: C49.2, R67.1, U6.2 (Trig), U6.6 (Thresh)
unnamed: C51.2, U6.5 (Cont)
unnamed: C52.2, R70.1, U7.2 (Trig), U7.6 (Thresh)
unnamed: C54.2, U7.5 (Cont)
unnamed: C55.2, R71.2, R72.1, R77.2, TP81.1, U8.2 (REF)
unnamed: D8.2 (A), R54.2, R55.2
unnamed: D9.2 (A), R57.2, R59.2
unnamed: D10.2 (A), R58.2, R60.2
unnamed: D12.2 (A), Q4.3, R56.1
unnamed: D13.2 (A), Q5.3, R61.1
unnamed: D14.1 (K), Q7.2, R65.2, R68.2
unnamed: Q4.1, R55.1
unnamed: Q5.1, R59.1
unnamed: Q6.1, R60.1, R62.2
unnamed: Q6.3, Q8.1, R68.1
unnamed: Q7.1, R64.2, R65.1
unnamed: Q8.3, R62.1, R64.1
unnamed: Q9.1, R73.2, R74.1, TP80.1
unnamed: Q9.3, S1.2
unnamed: Q10.1, R76.2
unnamed: Q11.1, R79.2, R80.1
unnamed: Q11.3, S2.2
unnamed: Q12.1, R82.2, R83.1
unnamed: Q12.3, S3.2
unnamed: Q13.1, R85.2, R86.1
unnamed: Q13.3, S4.2
unnamed: R66.1, R67.2, U6.7 (Disch)
unnamed: R69.1, R70.2, U7.7 (Disch)
unnamed: R73.1, U7.3 (Q)
unnamed: R75.1, R76.1, U8.1 (K)
unnamed: R77.1, R78.2
unnamed: U6.3 (Q), U7.4 (Reset)

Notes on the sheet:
Power-down alarm
C4 (~~261 Hz) oscillator
~~1 Hz oscillator
Threshold ~~2.4-2.9V
Sounds power-down alarm (powered from alarm battery) if any of the main power rails go down
Threshold ~~3.5-4.2V
10K resistors provide ~~50uA nominal through zeners near threshold input voltage; 1K resistor provides ~~0.5mA through BAS21 near threshold input voltage
~~1 ms filter
All 2.4 kHz, 88 dbA @ 5V
Software alarms
Power ORing from alarm battery
PNP circuit disables alarm battery output when +5V is present, even though battery voltage is higher than 5V
~~0.6 mA battery load
Optional hysteresis
Low alarm battery monitor
Low battery threshold 5.1V (semi-arbitrary) Threshold ~~= 2.495V * ((Rlow||Rhyst)+Rhigh)/(Rlow||Rhyst)
~~38-75 mV hysteresis (on REF pin) Hysteresis = (+5V_Batt - 2.495V)/Rhyst*(Rhigh || Rlow) (only valid @ trip point when TL431's REF pin = 2.495V; larger hysteresis when REF voltage is lower because battery voltage is << threshold voltage)
Limits current to FPGA and/or CC and/or RPi input (150µA max.), clamped to 3.3V by ext. Schottkys
~~25µA battery load
1 mA min. required cathode current when on, 1 µA max. cathode current drawn when off
Rlow
Rhigh
0.4µA max. into ref. pin
On: Cathode current = 2.2 mA (low batt.) to 4.4 mA (+5V) Vbe=1.5V min. (before resistor) → Ib=150µA min. Off: Vbe < 1 mV
Rhyst
+5V_Batt voltage range is about 4V (+5V minus large diode Vf) to 5.5V (6V battery minus small diode Vf)
Alternate output for indicator LED, etc.
2mA Ib, can support ~~200 mA load on +5V_Batt

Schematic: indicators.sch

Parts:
J11: Cable to indicator board; Molex_Micro-Fit_3.0_43650-0815_1x08_P3.00mm_Vertical; Manufacturer PN 43650-0815

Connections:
+5V: J11.2; also elsewhere on the board
/CC-LED-G: J11.3; also elsewhere on the board
/CC-LED-R: J11.4; also elsewhere on the board
/CC-LED-Y: J11.5; also elsewhere on the board
/UI-LED-G: J11.6; also elsewhere on the board
/UI-LED-R: J11.7; also elsewhere on the board
/UI-LED-Y: J11.8; also elsewhere on the board
GND: J11.1; also elsewhere on the board

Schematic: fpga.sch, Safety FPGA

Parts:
H15: FPGAOutline; BEMICRO-MAX10
J12: Mates J4 on BeMicro MAX10; PinSocket_2x20_P2.54mm_Vertical; Manufacturer PN ESW-120-33-G-D
J13: Mates J5 on BeMicro MAX10; PinSocket_2x20_P2.54mm_Vertical; Manufacturer PN ESW-120-33-G-D
R87, R88: 4.7k; R_0603_1608Metric
R89: 0; R_1206_3216Metric

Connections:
+5V: R89.2; also elsewhere on the board
/FPGA-Buzzer: J13.1; also elsewhere on the board
/FPGA-Stepper-Reset: J13.7; also elsewhere on the board
/Safety FPGA/DIFF-RX-0+: J13.39
/Safety FPGA/DIFF-RX-0-: J13.40
/Safety FPGA/DIFF-RX-1+: J13.37
/Safety FPGA/DIFF-RX-1-: J13.38
/Safety FPGA/DIFF-RX-2+: J13.35
/Safety FPGA/DIFF-RX-2-: J13.36
/Safety FPGA/DIFF-RX-3+: J13.33
/Safety FPGA/DIFF-RX-3-: J13.34
/Safety FPGA/DIFF-RX-4+: J13.31
/Safety FPGA/DIFF-RX-4-: J13.32
/Safety FPGA/DIFF-RX-5+: J13.27
/Safety FPGA/DIFF-RX-5-: J13.28
/Safety FPGA/DIFF-RX-6+: J13.25
/Safety FPGA/DIFF-RX-6-: J13.26
/Safety FPGA/DIFF-RX-7+: J13.23; also elsewhere on the board
/Safety FPGA/DIFF-RX-7-: J13.24; also elsewhere on the board
/Safety FPGA/DIFF-RX-8+: J13.21; also elsewhere on the board
/Safety FPGA/DIFF-RX-8-: J13.22; also elsewhere on the board
/Safety FPGA/DIFF-RX-9+: J13.19; also elsewhere on the board
/Safety FPGA/DIFF-RX-9-: J13.20; also elsewhere on the board
/Safety FPGA/DIFF-RX-A+: J13.17; also elsewhere on the board
/Safety FPGA/DIFF-RX-A-: J13.18; also elsewhere on the board
/Safety FPGA/DIFF-RX-B+: J13.15; also elsewhere on the board
/Safety FPGA/DIFF-RX-B-: J13.16; also elsewhere on the board
/Safety FPGA/GPIO-11: J13.13; also elsewhere on the board
/Safety FPGA/GPIO-12: J13.14; also elsewhere on the board
/Safety FPGA/GPIO-A: J12.5
/Safety FPGA/GPIO-B: J12.6
/Safety FPGA/I2C-SCL-FPGA: J12.4, R88.2; also elsewhere on the board
/Safety FPGA/I2C-SDA-FPGA: J12.3, R87.2; also elsewhere on the board
/Safety FPGA/LVDS-TX-0+: J12.40
/Safety FPGA/LVDS-TX-0-: J12.39
/Safety FPGA/LVDS-TX-1+: J12.38
/Safety FPGA/LVDS-TX-1-: J12.37
/Safety FPGA/LVDS-TX-2+: J12.36
/Safety FPGA/LVDS-TX-2-: J12.35
/Safety FPGA/LVDS-TX-3+: J12.32
/Safety FPGA/LVDS-TX-3-: J12.31
/Safety FPGA/LVDS-TX-4+: J12.30
/Safety FPGA/LVDS-TX-4-: J12.29
/Safety FPGA/LVDS-TX-5+: J12.28
/Safety FPGA/LVDS-TX-5-: J12.27
/Safety FPGA/LVDS-TX-6+: J12.24
/Safety FPGA/LVDS-TX-6-: J12.23
/Safety FPGA/LVDS-TX-7+: J12.22
/Safety FPGA/LVDS-TX-7-: J12.21
/Safety FPGA/LVDS-TX-8+: J12.20
/Safety FPGA/LVDS-TX-8-: J12.19
/Safety FPGA/LVDS-TX-9+: J12.16
/Safety FPGA/LVDS-TX-9-: J12.15
/Safety FPGA/LVDS-TX-A+: J12.14
/Safety FPGA/LVDS-TX-A-: J12.13
/Safety FPGA/LVDS-TX-B+: J12.12
/Safety FPGA/LVDS-TX-B-: J12.11
/UART-CTS-STM-RTS-FPGA: J13.9; also elsewhere on the board
/UART-RTS-STM-CTS-FPGA: J13.8; also elsewhere on the board
/UART-Rx-FPGA-Tx-RPi: J13.5; also elsewhere on the board
/UART-Rx-STM-Tx-FPGA: J13.3; also elsewhere on the board
/UART-Tx-FPGA-Rx-RPi: J13.6; also elsewhere on the board
/UART-Tx-STM-Rx-FPGA: J13.4; also elsewhere on the board
/UI-Power-Off: J13.2; also elsewhere on the board
/VSys-Power-Off: J13.10; also elsewhere on the board
GND: J12.7, J12.8, J12.9, J12.10, J12.17, J12.18, J12.25, J12.26, J12.33, J12.34, J13.12, J13.30; also elsewhere on the board
unnamed: J13.11, R89.1

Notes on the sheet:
+3.3V_FPGA comes from FPGA board
Place for optional fuse
BeMicro MAX10 board has onboard I2C pull-ups

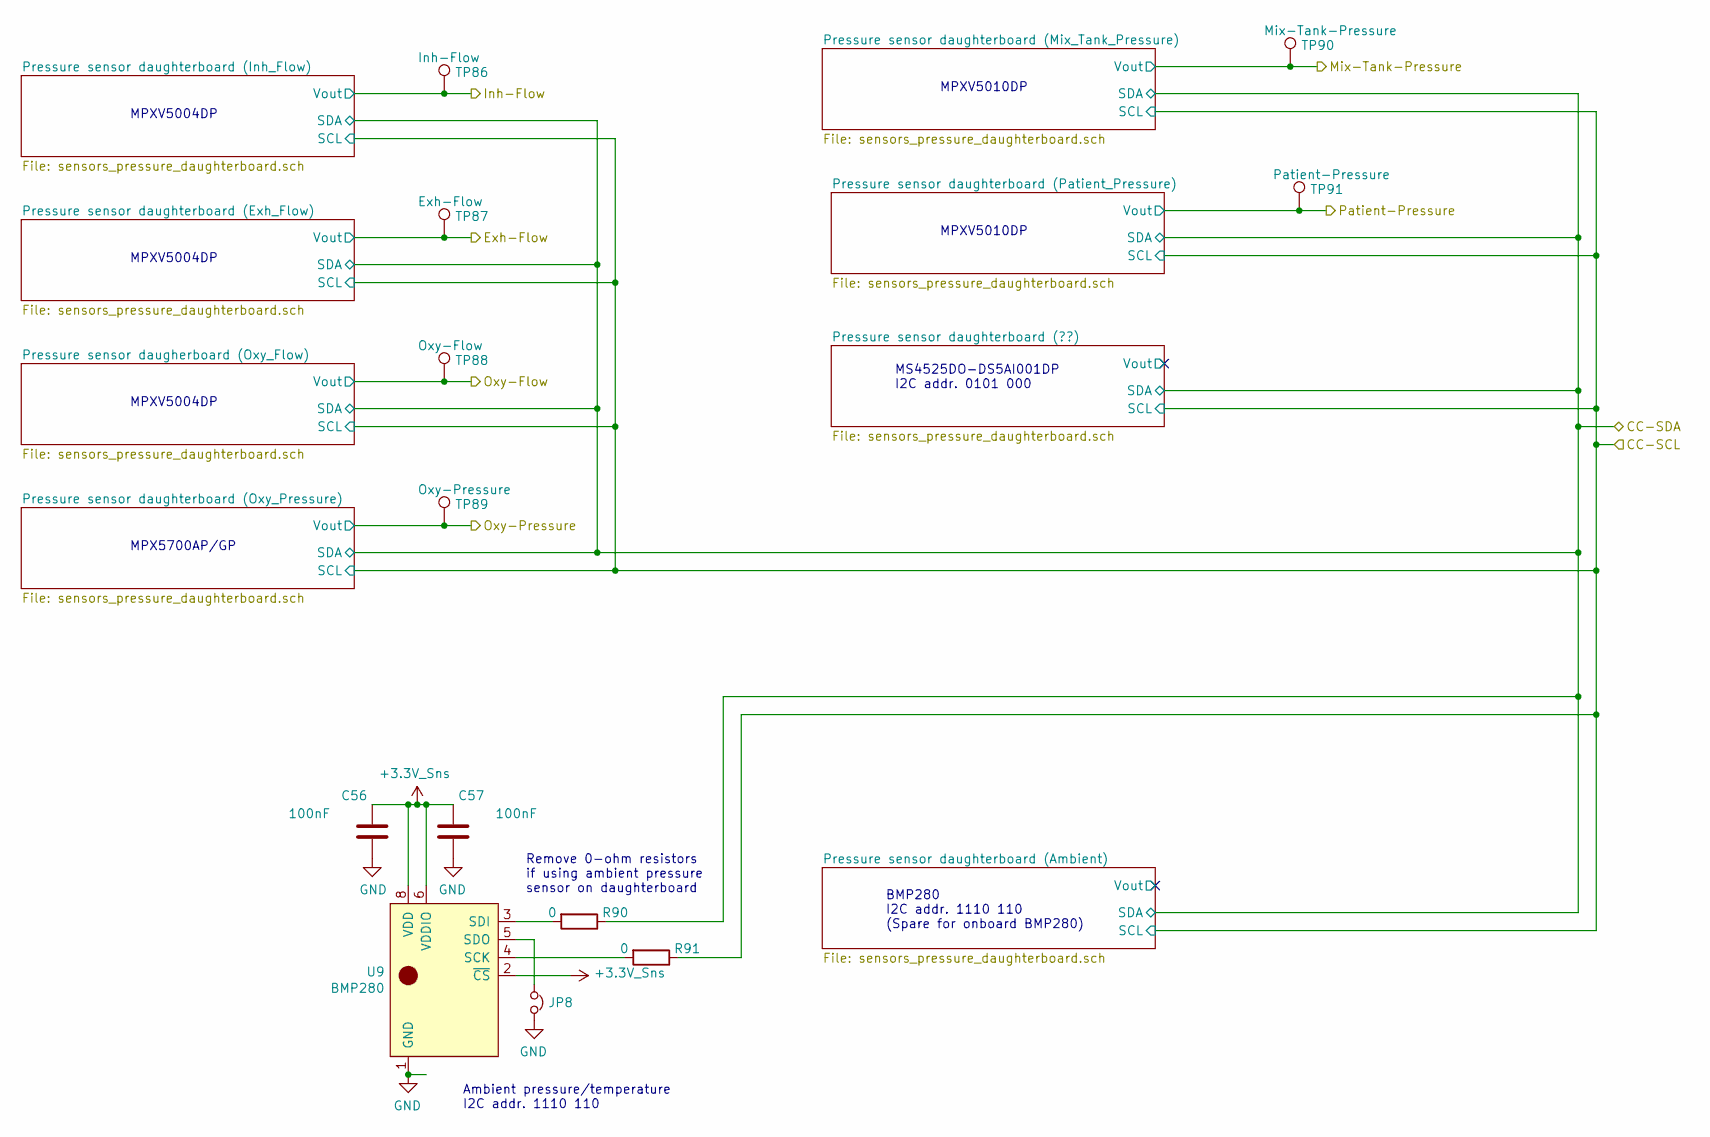
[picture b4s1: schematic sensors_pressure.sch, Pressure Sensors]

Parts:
C56, C57: 100nF; C_0603_1608Metric; Voltage 50V; Manufacturer PN C0603C104K5RACTU
JP8: Jumper_NC_Small; SolderJumper-2_P1.3mm_Bridged_RoundedPad1.0x1.5mm
R90, R91: 0; R_0603_1608Metric
TP86: Inh-Flow; TestPoint_Pad_2.0x2.0mm
TP87: Exh-Flow; TestPoint_Pad_2.0x2.0mm
TP88: Oxy-Flow; TestPoint_Pad_2.0x2.0mm
TP89: Oxy-Pressure; TestPoint_Pad_2.0x2.0mm
TP90: Mix-Tank-Pressure; TestPoint_Pad_2.0x2.0mm
TP91: Patient-Pressure; TestPoint_Pad_2.0x2.0mm
U9: BMP280; Bosch_BMP280; Manufacturer PN BMP280

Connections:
+3.3V_Sns: C56.2, C57.2, U9.2 (~CS), U9.6 (VDDIO), U9.8 (VDD); also elsewhere on the board
/CC-SCL: R91.1; also elsewhere on the board
/CC-SDA: R90.1; also elsewhere on the board
/Exh-Flow: TP87.1; also elsewhere on the board
/Inh-Flow: TP86.1; also elsewhere on the board
/Mix-Tank-Pressure: TP90.1; also elsewhere on the board
/Oxygen-Flow: TP88.1; also elsewhere on the board
/Oxygen-Pressure: TP89.1; also elsewhere on the board
/Patient-Pressure: TP91.1; also elsewhere on the board
GND: C56.1, C57.1, JP8.2, U9.1 (GND), U9.7; also elsewhere on the board
unnamed: JP8.1, U9.5 (SDO)
unnamed: R90.2, U9.3 (SDI)
unnamed: R91.2, U9.4 (SCK)

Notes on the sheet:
BMP280 I2C addr. 1110 110 (Spare for onboard BMP280)
MS4525DO-DS5AI001DP I2C addr. 0101 000
MPXV5004DP
MPX5700AP/GP
MPXV5010DP
Ambient pressure/temperature I2C addr. 1110 110
Remove 0-ohm resistors if using ambient pressure sensor on daughterboard

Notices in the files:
README.md:
License: Apache 2.0
